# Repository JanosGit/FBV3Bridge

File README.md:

# FBV3Bridge
PJRC Teensy 3.2 based device to interface a Line 6 FBV3 to a USB-Serial Port to access its functionality through Max for Live or Max/MSP

Inspired by some other projects out there ([this one by rasmartins](https://github.com/rasmartins/fbv2kpa) and [this one by wrbi](https://github.com/wrbi/FBV2MIDI)), that have successfully interfaced the older FBV-range boards, the goal of this project is to make use of the extended functionality of the FBV3 Board - most of all the RGB-LEDs.

Within this project, I'm responsible of designing the hardware that acts as bridge between your PC or Mac and ther Line 6 FBV3 Board. Most of the reverse engineering of the communication protocol and the design of an upcoming Max for Live device that lets you control Ableton Live with an FBV3 board is done by [Soundmanufacture](http://soundmanufacture.net/index.html).

## The Max Patcher

You'll find a first proof-of-cocept Max patcher that allows setting the colours of nearly all Button LEDs as well as reading the state of the buttons and the expression pedal in the "Max" subfolder of this repository.

## The hardware

Our first hardware prototype consists of a small PCB, interfacing two RS485 over RJ45 connections used by Line 6 to the Teensy on the one side and supplying an USB connection to connect with your computer on the other side. The two RJ45 connections were added to make it possible to attach the device between the floorboard and an original Line 6 amp and reord data traffic to make protocol reverse engineering possible. In a second mode of operation the device just initializes the FBV3 board as the amp would do and then acts as a transparent RS485 to serial bridge. 

The initial plan was to power the board via USB, however it seems that not all USB port supply enough current, so we had to modify the design to power it with an external 9V power adapter.

### Next hardware generation

After being successful in reverse-engineering the protocol we are currently planing a second hardware generation. Features of this new hardware should be

- More compact design, all components including the MCU and a proper power suply circuit on one board instead of plugging a Teensy onto the board
- Professional manufactured PCB instead of the home-made design of the prototype, making solering SMT components much easier
- 3D printed housing to make it finally suitable for stage-use
- Fix some minor errors in the schematics

News regarding the new designs will be posted here as soon as available

### Impressions of the prototype

Here are some pictures of the first version of the prototype that was still USB-Bus powered. You'll find the schematics in the "Hardware" subfolder of this repo.

### The software modes of the prototype
As said above, the software for the Teensy has two modes of operation: If both an amp and an FBV3 Board are plugged in, it logs the communication between the two endpoints and prints it in human-readable form to the USB-Serial output. If no amp is plugged in, it sends the same initialization-sequence an amp would send to the FBV3 board and redirects the in/out data streams byte-transparent to the USB-Serial port afterwards.

With the help of the first mode, the protocol of the FBV3 could be reverse-engineered.
Here you see a screenshot of the serial communication logged while the device was in the first mode.

In this mode, the amp and the FBV3 behave just like there wouldn't be anything more than a cable connecting them.
In the second mode, the Teensy sends an initialization sequence (actually, completely the same sequence as the Line 6 Spider Amp I had here sent - I just changed the content sent to the LCD display). So it boots up like this:

The current software is based on the Teensyduino environment and can be found in the "Software/FBV3Bridge" subfolder of this repository

## Known facts about the protocol

Each valid message seems to have the following structure:

| Start byte | Number of bytes following                        | Command type              | Parameters                 |
|:----------:|--------------------------------------------------|---------------------------|----------------------------|
| 0xF0       | Counted without this byte --> Message Length - 2 | e.g. 0x04 for Button LEDs | e.g. Button Number, On/Off |

These messages could already be identified:
### Switching Button LEDs

| 0xF0 | 0x03 | 0x04 | Button Number | 0x01 for "On", 0x00 for "Dark" (or "Off" if LED red), 0x02 for "Off" |
|:----:|:----:|:----:|:-------------:|:-------------------------------:|

### Setting Button LED Colours

| 0xF0 | 0x03 | 0x05 | Button Number | A value betweem 0x00 and 0x09 for 9 different colours |
|:----:|:----:|:----:|:-------------:|:-------------------------------:|

### First three display characters (-> The preset number)
Note: Although Line 6 uses this for the preset number, all possible ascii characters seem to be working here

| 0xF0 | 0x05 | 0x08 | 0x20 | character 1 | character 2 | character 3 |
|:----:|:----:|:----:|:----:|:-----------:|:-----------:|:-----------:|

### The remaining display text
Note: It seems to be unavoidable that there is a whitespace between the first three characters of the preset nubmer and the remainig display text

| 0xF0 | text length + 3 | 0x10 | 0x00 | 0x01 | the text as ascii string |
|:----:|:---------------:|:----:|:----:|:----:|:------------------------:|

Note that

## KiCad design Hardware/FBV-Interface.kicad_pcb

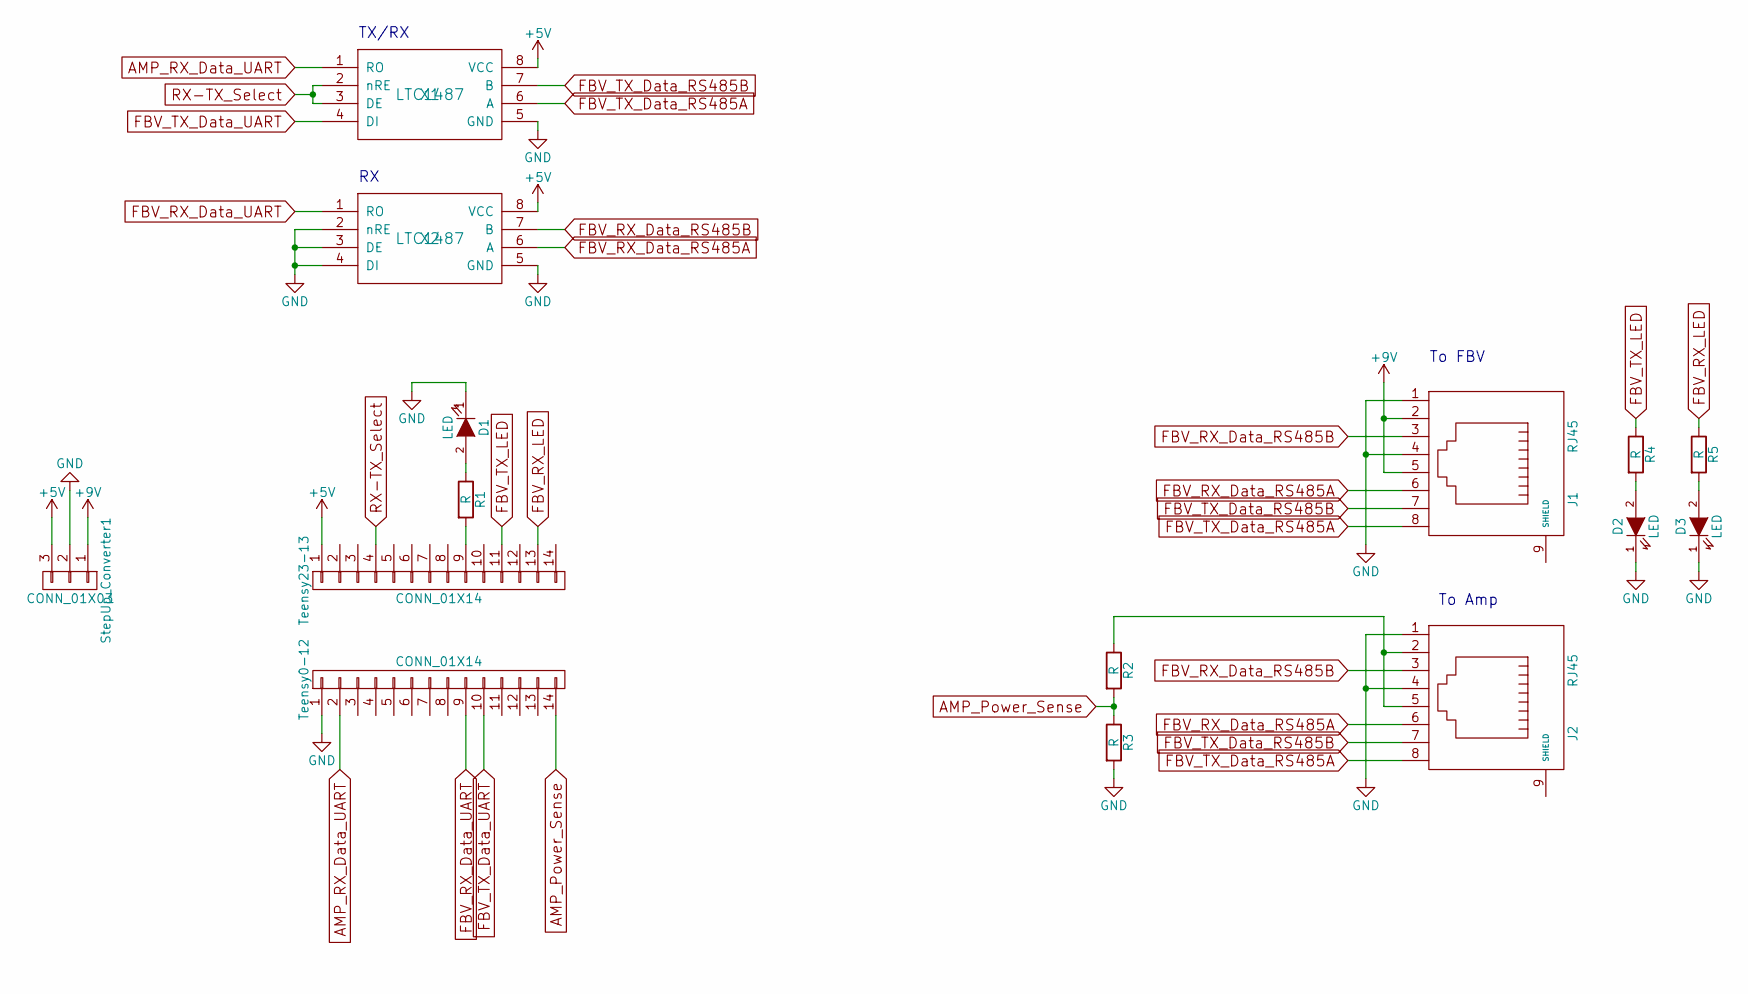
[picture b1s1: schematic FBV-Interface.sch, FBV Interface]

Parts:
D1, D2, D3: LED; LED-3MM
J1, J2: RJ45; RJ45_8
R1, R2, R3, R4, R5: R; R_1206_HandSoldering
StepUp_Converter1: CONN_01X03; Pin_Header_Straight_1x03
Teensy0-12, Teensy23-13: CONN_01X14; Pin_Header_Straight_1x14
X1, X2: LTC1487

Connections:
+5V: StepUp_Converter1.3, Teensy23-13.1, X1.8 (VCC), X2.8 (VCC)
+9V: J1.2, J1.5, StepUp_Converter1.1
AMP_Power_Sense: R2.2, R3.1, Teensy0-12.14
AMP_RX_Data_UART: Teensy0-12.2, X1.1 (RO)
FBV_RX_Data_RS485A: J1.6, J2.6, X2.6 (A)
FBV_RX_Data_RS485B: J1.3, J2.3, X2.7 (B)
FBV_RX_Data_UART: Teensy0-12.9, X2.1 (RO)
FBV_RX_LED: R5.1, Teensy23-13.13
FBV_TX_Data_RS485A: J1.8, J2.8, X1.6 (A)
FBV_TX_Data_RS485B: J1.7, J2.7, X1.7 (B)
FBV_TX_Data_UART: Teensy0-12.10, X1.4 (DI)
FBV_TX_LED: R4.1, Teensy23-13.11
GND: D1.1 (K), D2.1 (K), D3.1 (K), J1.1, J1.4, J2.1, J2.4, R3.2, StepUp_Converter1.2, Teensy0-12.1, X1.5 (GND), X2.2 (nRE), X2.3 (DE), X2.4 (DI), X2.5 (GND)
unnamed: D1.2 (A), R1.1
unnamed: D2.2 (A), R4.2
unnamed: D3.2 (A), R5.2
unnamed: J2.2, J2.5, R2.1
unnamed: R1.2, Teensy23-13.9
RX-TX_Select: Teensy23-13.4, X1.2 (nRE), X1.3 (DE)

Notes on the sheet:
To FBV
TX/RX
To Amp

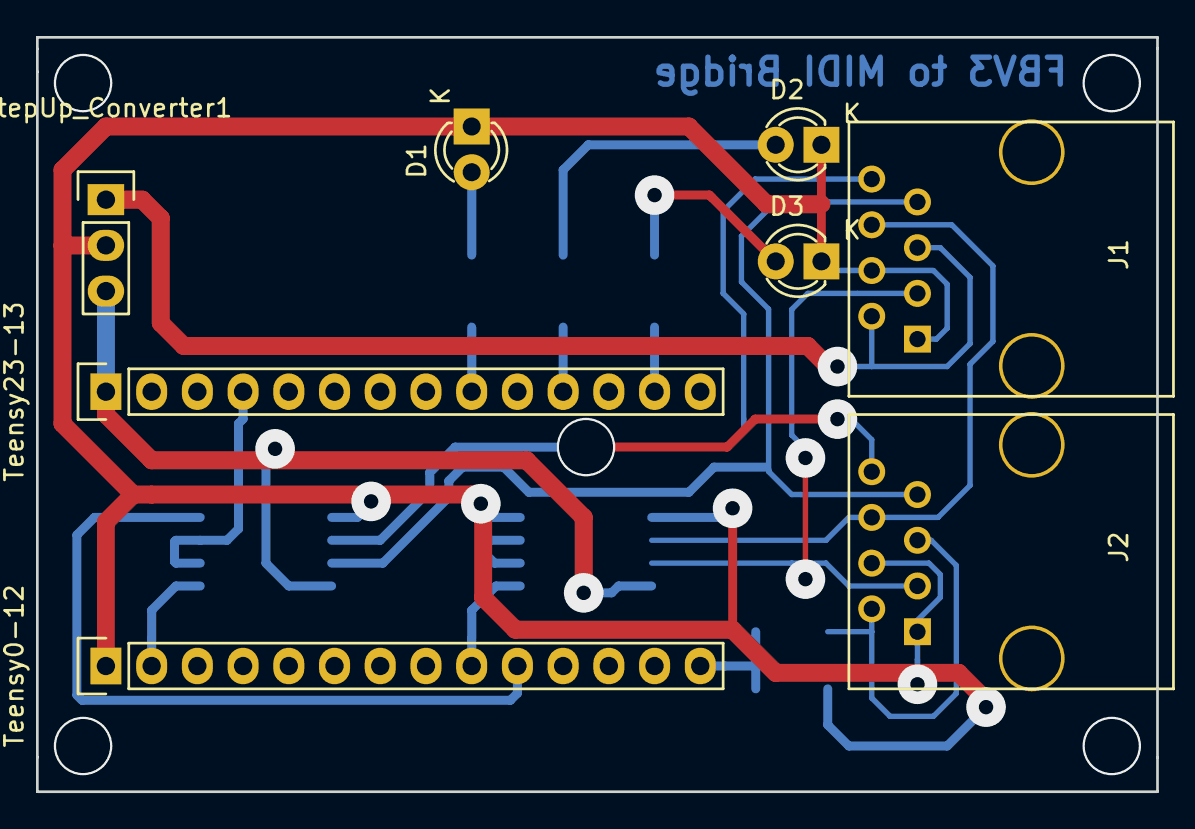
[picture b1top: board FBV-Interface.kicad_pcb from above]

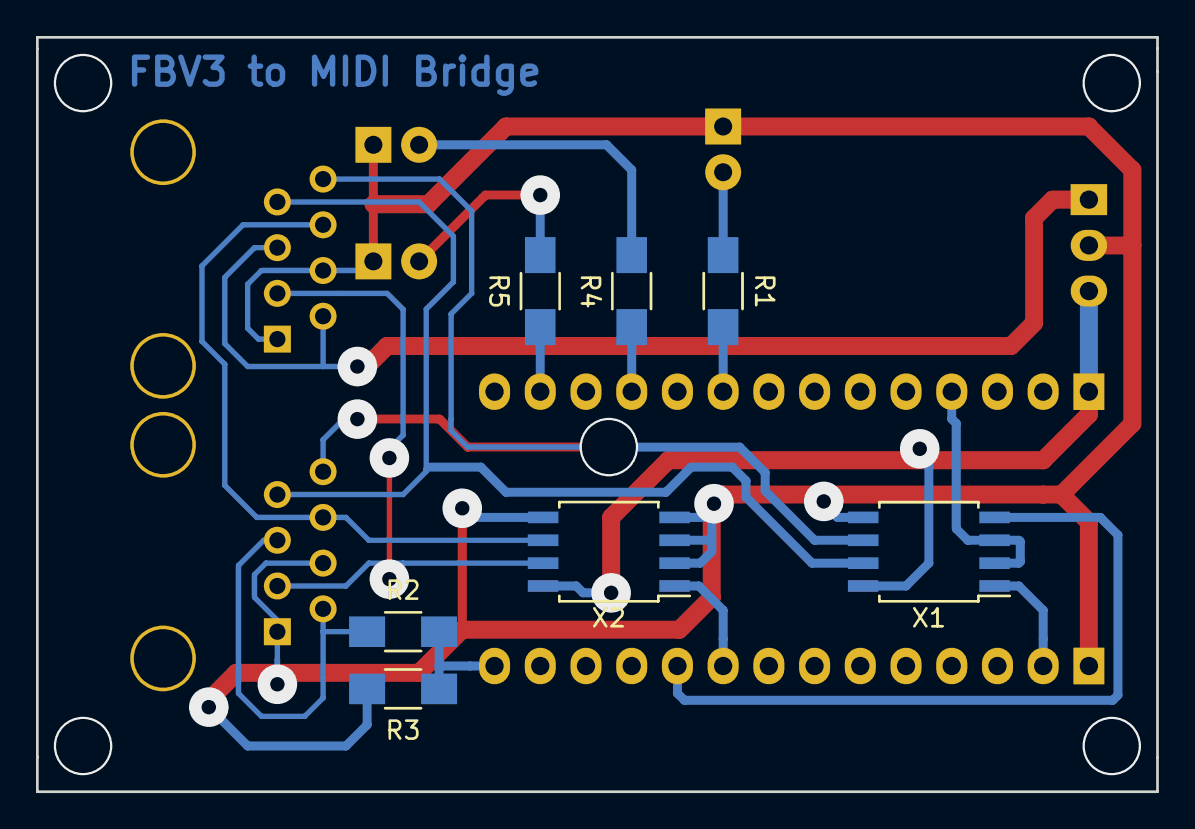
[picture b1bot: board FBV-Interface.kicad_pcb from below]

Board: 2 copper layers, 62.2 x 41.9 mm, 15 parts (7 on the bottom side), 19 nets.

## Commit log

2017-07-28 First stable version
2017-07-28 Created a readme
2017-07-28 Added some additional ressources
2017-07-28 Github doesn't like tiff images...
2017-07-31 Added Max demo patcher
2017-07-31 Fixed a typo
2017-07-31 Added picture of FBV3 with default startup Message in LCD
2017-07-31 Added some facts about the protocol
2017-08-07 Created a readme for Reverse Engineering folder
2019-08-11 Updated Readme & Max Patcher
2019-08-27 Fixed an image not being displayed in the Readme
